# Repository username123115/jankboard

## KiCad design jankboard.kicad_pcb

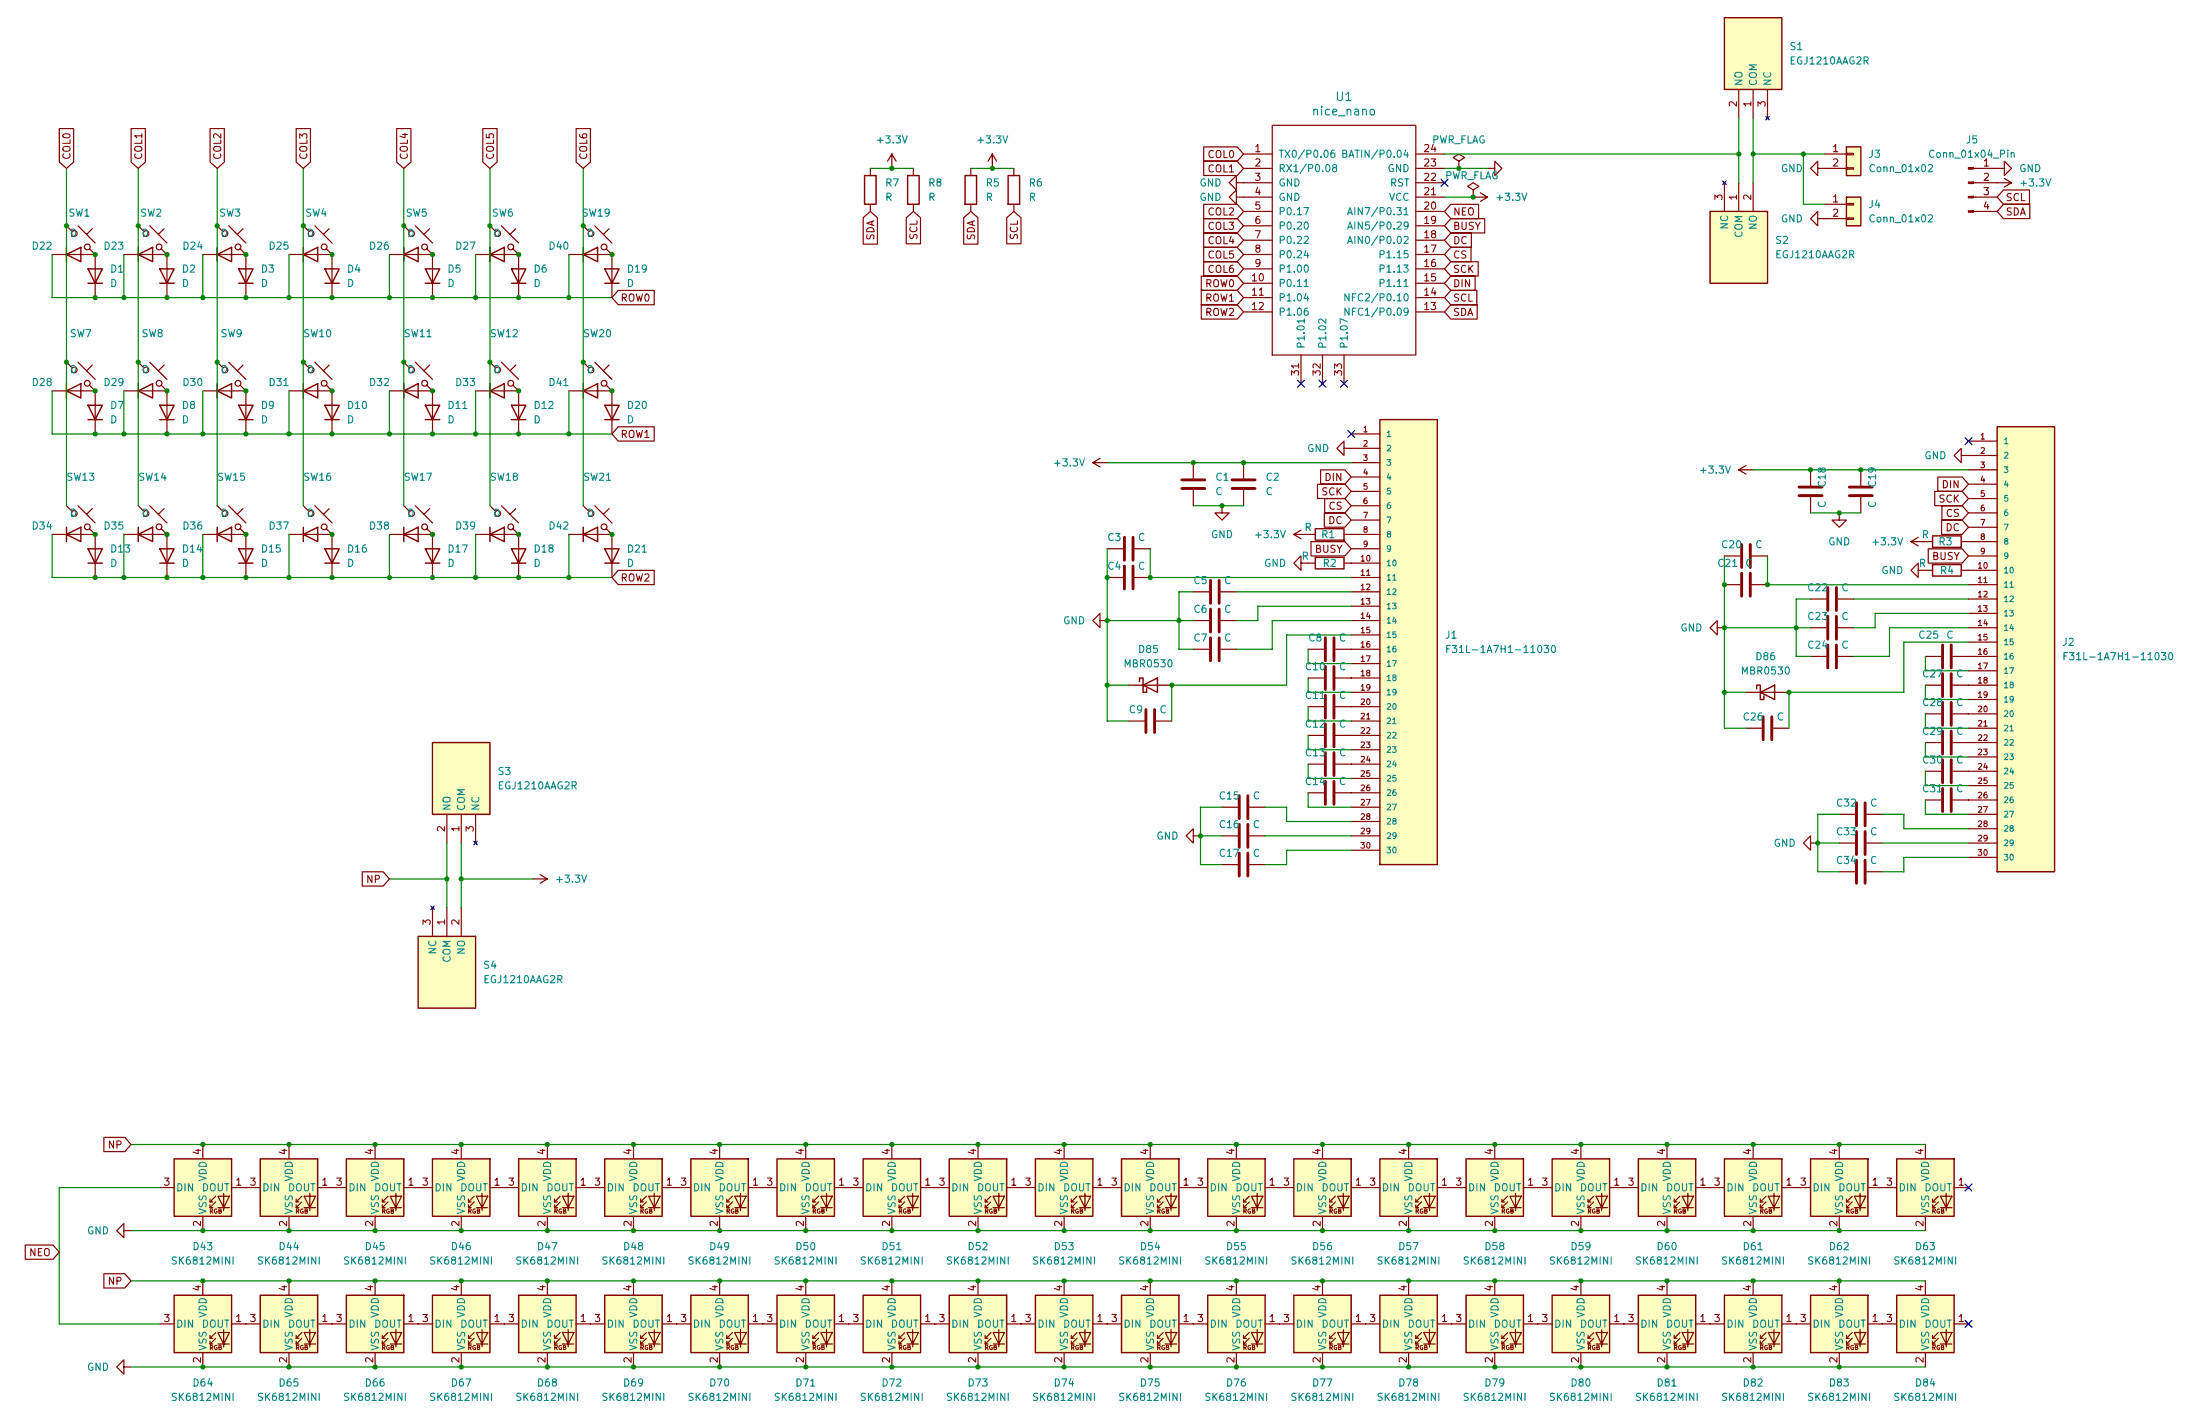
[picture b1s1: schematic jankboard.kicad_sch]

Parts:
C1, C2, C3, C4, C5, C6, C7, C8, C9, C10, C11, C12, C13, C14, C15, C16, C17, C18, C19, C20, C21, C22, C23, C24, C25, C26, C27, C28, C29, C30, C31, C32, C33, C34: C; C_0603_1608Metric
D1, D2, D3, D4, D5, D6, D7, D8, D9, D10, D11, D12, D13, D14, D15, D16, D17, D18, D19, D20, D21, D22, D23, D24, D25, D26, D27, D28, D29, D30, D31, D32, D33, D34, D35, D36, D37, D38, D39, D40, D41, D42: D; D_1206_3216Metric
D43, D44, D45, D46, D47, D48, D49, D50, D51, D52, D53, D54, D55, D56, D57, D58, D59, D60, D61, D62, D63, D64, D65, D66, D67, D68, D69, D70, D71, D72, D73, D74, D75, D76, D77, D78, D79, D80, D81, D82, D83, D84: SK6812MINI; LED_SK6812MINI_PLCC4_3.5x3.5mm_P1.75mm
D85, D86: MBR0530; D_SOD-123
J1, J2: F31L-1A7H1-11030; PARTREV L
J3, J4: Conn_01x02; JST_PH_S2B-PH-SM4-TB_1x02-1MP_P2.00mm_Horizontal
J5: Conn_01x04_Pin; PinHeader_1x04_P2.54mm_Vertical
R1, R2, R3, R4, R5, R6, R7, R8: R; R_0603_1608Metric
S1, S2, S3, S4: EGJ1210AAG2R; Manufacturer_Part_Number EGJ1210AAG2R
SW1, SW2, SW3, SW4, SW5, SW6, SW7, SW8, SW9, SW10, SW11, SW12, SW13, SW14, SW15, SW16, SW17, SW18, SW19, SW20, SW21: SW_Push_45deg; SW_PG1350_reversible
U1: nice_nano

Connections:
+3.3V: C1.1, C2.1, C18.1, C19.1, J1.3, J2.3, J5.2, R1.1, R3.1, R5.1, R6.1, R7.1, R8.1, S3.1 (COM), S4.2 (NO), U1.21 (VCC)
BUSY: J1.9, J2.9, U1.19 (AIN5/P0.29)
COL0: SW1.1, SW7.1, SW13.1, U1.1 (TX0/P0.06)
COL1: SW2.1, SW8.1, SW14.1, U1.2 (RX1/P0.08)
COL2: SW3.1, SW9.1, SW15.1, U1.5 (P0.17)
COL3: SW4.1, SW10.1, SW16.1, U1.6 (P0.20)
COL4: SW5.1, SW11.1, SW17.1, U1.7 (P0.22)
COL5: SW6.1, SW12.1, SW18.1, U1.8 (P0.24)
COL6: SW19.1, SW20.1, SW21.1, U1.9 (P1.00)
CS: J1.6, J2.6, U1.17 (P1.15)
DC: J1.7, J2.7, U1.18 (AIN0/P0.02)
DIN: J1.4, J2.4, U1.15 (P1.11)
GND: C1.2, C2.2, C3.1, C4.1, C5.1, C6.1, C7.1, C9.1, C15.1, C16.1, C17.1, C18.2, C19.2, C20.1, C21.1, C22.1, C23.1, C24.1, C26.1, C32.1, C33.1, C34.1, D43.2 (VSS), D44.2 (VSS), D45.2 (VSS), D46.2 (VSS), D47.2 (VSS), D48.2 (VSS), D49.2 (VSS), D50.2 (VSS), D51.2 (VSS), D52.2 (VSS), D53.2 (VSS), D54.2 (VSS), D55.2 (VSS), D56.2 (VSS), D57.2 (VSS), D58.2 (VSS), D59.2 (VSS), D60.2 (VSS), D61.2 (VSS), D62.2 (VSS), D63.2 (VSS), D64.2 (VSS), D65.2 (VSS), D66.2 (VSS), D67.2 (VSS), D68.2 (VSS), D69.2 (VSS), D70.2 (VSS), D71.2 (VSS), D72.2 (VSS), D73.2 (VSS), D74.2 (VSS), D75.2 (VSS), D76.2 (VSS), D77.2 (VSS), D78.2 (VSS), D79.2 (VSS), D80.2 (VSS), D81.2 (VSS), D82.2 (VSS), D83.2 (VSS), D84.2 (VSS), D85.1 (K), D86.1 (K), J1.2, J2.2, J3.2, J4.2, J5.1, R2.2, R4.2, U1.3 (GND), U1.4 (GND), U1.23 (GND)
NEO: D43.3 (DIN), D64.3 (DIN), U1.20 (AIN7/P0.31)
NP: D43.4 (VDD), D44.4 (VDD), D45.4 (VDD), D46.4 (VDD), D47.4 (VDD), D48.4 (VDD), D49.4 (VDD), D50.4 (VDD), D51.4 (VDD), D52.4 (VDD), D53.4 (VDD), D54.4 (VDD), D55.4 (VDD), D56.4 (VDD), D57.4 (VDD), D58.4 (VDD), D59.4 (VDD), D60.4 (VDD), D61.4 (VDD), D62.4 (VDD), D63.4 (VDD), D64.4 (VDD), D65.4 (VDD), D66.4 (VDD), D67.4 (VDD), D68.4 (VDD), D69.4 (VDD), D70.4 (VDD), D71.4 (VDD), D72.4 (VDD), D73.4 (VDD), D74.4 (VDD), D75.4 (VDD), D76.4 (VDD), D77.4 (VDD), D78.4 (VDD), D79.4 (VDD), D80.4 (VDD), D81.4 (VDD), D82.4 (VDD), D83.4 (VDD), D84.4 (VDD), S3.2 (NO), S4.1 (COM)
unnamed: C3.2, C4.2, J1.11
unnamed: C5.2, J1.12
unnamed: C6.2, J1.13
unnamed: C7.2, J1.14
unnamed: C8.1, J1.17
unnamed: C8.2, J1.16
unnamed: C10.1, J1.19
unnamed: C10.2, J1.18
unnamed: C11.1, J1.21
unnamed: C11.2, J1.20
unnamed: C12.1, J1.23
unnamed: C12.2, J1.22
unnamed: C13.1, J1.25
unnamed: C13.2, J1.24
unnamed: C14.1, J1.27
unnamed: C14.2, J1.26
unnamed: C15.2, J1.28
unnamed: C16.2, J1.29
unnamed: C17.2, J1.30
unnamed: C20.2, C21.2, J2.11
unnamed: C22.2, J2.12
unnamed: C23.2, J2.13
unnamed: C24.2, J2.14
unnamed: C25.1, J2.17
unnamed: C25.2, J2.16
unnamed: C27.1, J2.19
unnamed: C27.2, J2.18
unnamed: C28.1, J2.21
unnamed: C28.2, J2.20
unnamed: C29.1, J2.23
unnamed: C29.2, J2.22
unnamed: C30.1, J2.25
unnamed: C30.2, J2.24
unnamed: C31.1, J2.27
unnamed: C31.2, J2.26
unnamed: C32.2, J2.28
unnamed: C33.2, J2.29
unnamed: C34.2, J2.30
unnamed: D1.2 (A), D22.2 (A), SW1.2
unnamed: D2.2 (A), D23.2 (A), SW2.2
unnamed: D10.2 (A), D31.2 (A), SW10.2
unnamed: D11.2 (A), D32.2 (A), SW11.2
unnamed: D12.2 (A), D33.2 (A), SW12.2
unnamed: D13.2 (A), D34.2 (A), SW13.2
unnamed: D14.2 (A), D35.2 (A), SW14.2
unnamed: D15.2 (A), D36.2 (A), SW15.2
unnamed: D16.2 (A), D37.2 (A), SW16.2
unnamed: D17.2 (A), D38.2 (A), SW17.2
unnamed: D18.2 (A), D39.2 (A), SW18.2
unnamed: D19.2 (A), D40.2 (A), SW19.2
unnamed: D20.2 (A), D41.2 (A), SW20.2
unnamed: D21.2 (A), D42.2 (A), SW21.2
unnamed: D3.2 (A), D24.2 (A), SW3.2
unnamed: D4.2 (A), D25.2 (A), SW4.2
unnamed: D5.2 (A), D26.2 (A), SW5.2
unnamed: D6.2 (A), D27.2 (A), SW6.2
unnamed: D7.2 (A), D28.2 (A), SW7.2
unnamed: D8.2 (A), D29.2 (A), SW8.2
unnamed: D9.2 (A), D30.2 (A), SW9.2
unnamed: D43.1 (DOUT), D44.3 (DIN)
unnamed: D44.1 (DOUT), D45.3 (DIN)
unnamed: D45.1 (DOUT), D46.3 (DIN)
unnamed: D46.1 (DOUT), D47.3 (DIN)
unnamed: D47.1 (DOUT), D48.3 (DIN)
unnamed: D48.1 (DOUT), D49.3 (DIN)
unnamed: D49.1 (DOUT), D50.3 (DIN)
unnamed: D50.1 (DOUT), D51.3 (DIN)
unnamed: D51.1 (DOUT), D52.3 (DIN)
unnamed: D52.1 (DOUT), D53.3 (DIN)
unnamed: D53.1 (DOUT), D54.3 (DIN)
unnamed: D54.1 (DOUT), D55.3 (DIN)
unnamed: D55.1 (DOUT), D56.3 (DIN)
unnamed: D56.1 (DOUT), D57.3 (DIN)
unnamed: D57.1 (DOUT), D58.3 (DIN)
unnamed: D58.1 (DOUT), D59.3 (DIN)
unnamed: D59.1 (DOUT), D60.3 (DIN)
unnamed: D60.1 (DOUT), D61.3 (DIN)
unnamed: D61.1 (DOUT), D62.3 (DIN)
unnamed: D62.1 (DOUT), D63.3 (DIN)
unnamed: D64.1 (DOUT), D65.3 (DIN)
unnamed: D65.1 (DOUT), D66.3 (DIN)
unnamed: D66.1 (DOUT), D67.3 (DIN)
unnamed: D67.1 (DOUT), D68.3 (DIN)
unnamed: D68.1 (DOUT), D69.3 (DIN)
unnamed: D69.1 (DOUT), D70.3 (DIN)
unnamed: D70.1 (DOUT), D71.3 (DIN)
unnamed: D71.1 (DOUT), D72.3 (DIN)
unnamed: D72.1 (DOUT), D73.3 (DIN)
unnamed: D73.1 (DOUT), D74.3 (DIN)
unnamed: D74.1 (DOUT), D75.3 (DIN)
unnamed: D75.1 (DOUT), D76.3 (DIN)
unnamed: D76.1 (DOUT), D77.3 (DIN)
unnamed: D77.1 (DOUT), D78.3 (DIN)
unnamed: D78.1 (DOUT), D79.3 (DIN)
unnamed: D79.1 (DOUT), D80.3 (DIN)
unnamed: D80.1 (DOUT), D81.3 (DIN)
unnamed: D81.1 (DOUT), D82.3 (DIN)
unnamed: D82.1 (DOUT), D83.3 (DIN)
unnamed: D83.1 (DOUT), D84.3 (DIN)
unnamed: C9.2, D85.2 (A), J1.15
unnamed: C26.2, D86.2 (A), J2.15
unnamed: J1.8, R1.2
unnamed: J1.10, R2.1
unnamed: J2.8, R3.2
unnamed: J2.10, R4.1
unnamed: J3.1, J4.1, S1.1 (COM), S2.2 (NO)
unnamed: S1.2 (NO), S2.1 (COM), U1.24 (BATIN/P0.04)
ROW0: D1.1 (K), D2.1 (K), D3.1 (K), D4.1 (K), D5.1 (K), D6.1 (K), D19.1 (K), D22.1 (K), D23.1 (K), D24.1 (K), D25.1 (K), D26.1 (K), D27.1 (K), D40.1 (K), U1.10 (P0.11)
ROW1: D7.1 (K), D8.1 (K), D9.1 (K), D10.1 (K), D11.1 (K), D12.1 (K), D20.1 (K), D28.1 (K), D29.1 (K), D30.1 (K), D31.1 (K), D32.1 (K), D33.1 (K), D41.1 (K), U1.11 (P1.04)
ROW2: D13.1 (K), D14.1 (K), D15.1 (K), D16.1 (K), D17.1 (K), D18.1 (K), D21.1 (K), D34.1 (K), D35.1 (K), D36.1 (K), D37.1 (K), D38.1 (K), D39.1 (K), D42.1 (K), U1.12 (P1.06)
SCK: J1.5, J2.5, U1.16 (P1.13)
SCL: J5.3, R6.2, R8.2, U1.14 (NFC2/P0.10)
SDA: J5.4, R5.2, R7.2, U1.13 (NFC1/P0.09)

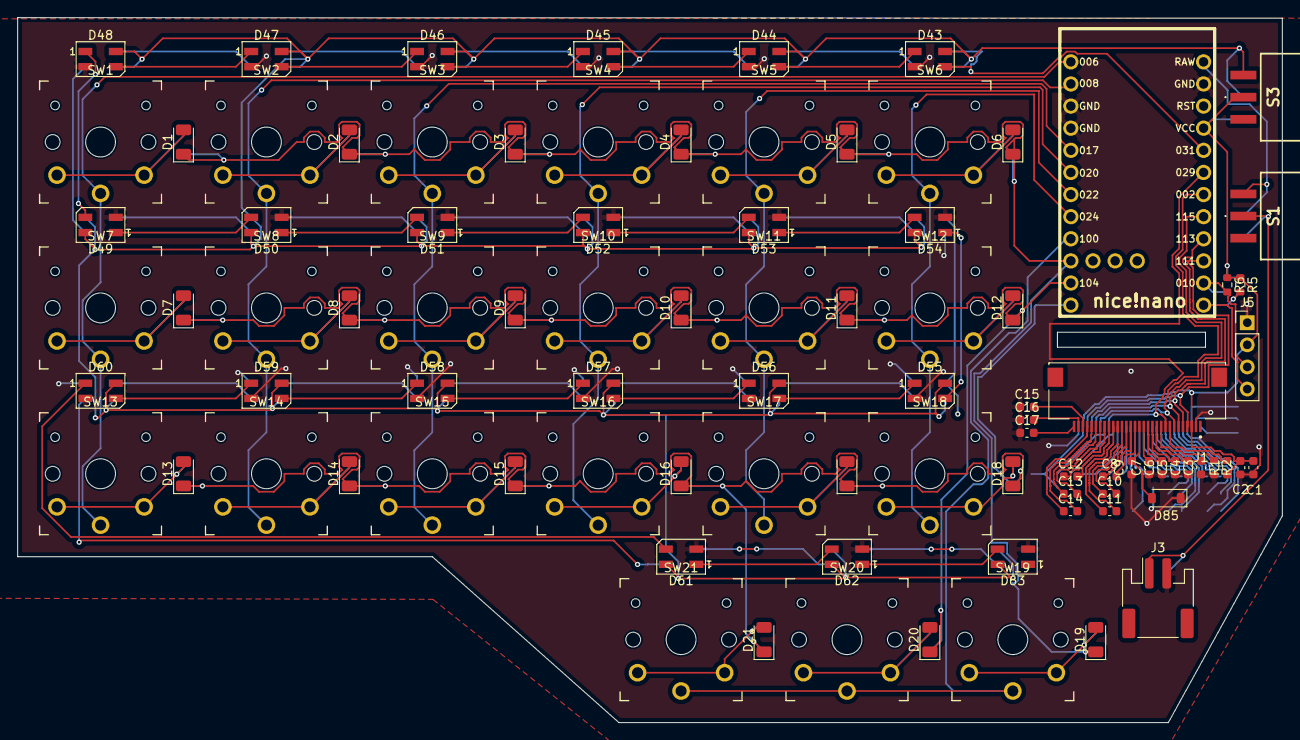
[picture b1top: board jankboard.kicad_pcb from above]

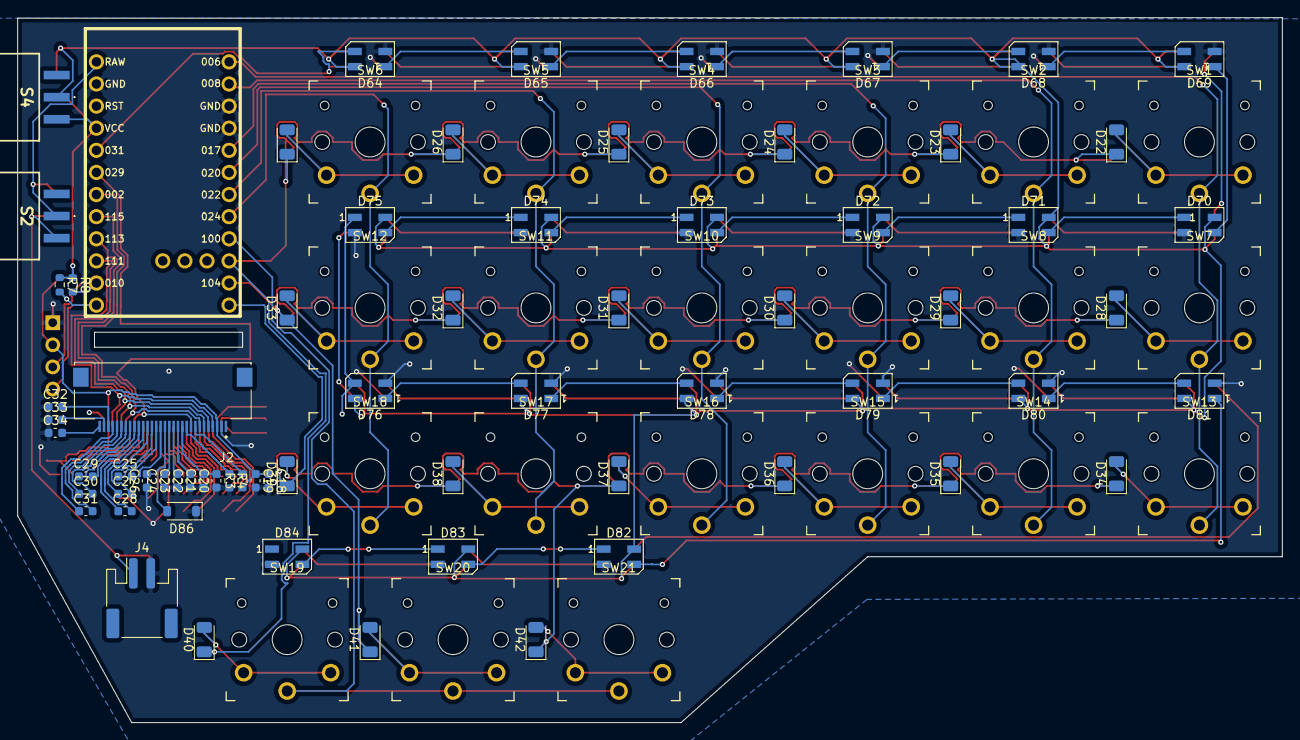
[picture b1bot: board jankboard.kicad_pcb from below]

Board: 2 copper layers, 145.3 x 81.0 mm, 159 parts (68 on the bottom side), 128 nets.

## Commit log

2025-03-02 add libraries
2025-03-02 add symbols again
2025-03-06 gross shcematiasdf
2025-03-06 add low profile switch library
2025-03-06 place keys and leds
2025-03-06 wired up matrix
2025-03-06 neopixels
2025-03-07 connectors
2025-03-07 design rule checking
2025-03-10 remove via on pins, change pin footprint
2025-03-10 add led switch
2025-03-10 add models
2025-03-10 make room for hole
2025-03-10 add hole
2025-03-10 elongate holes slightly for better clearance of fpc cable
